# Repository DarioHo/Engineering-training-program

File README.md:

# Engineering-training-program

This is the Engineering training course that consists of three modules: Internet of Things, Microcontroller and Arduino, 
printed circuit board.

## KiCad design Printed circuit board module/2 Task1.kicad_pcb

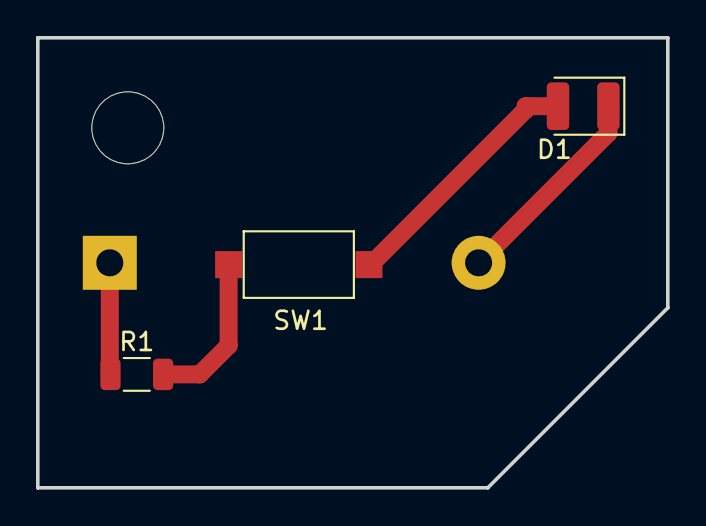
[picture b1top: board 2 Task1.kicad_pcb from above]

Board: 2 copper layers, 35.0 x 25.0 mm, 5 parts (1 on the bottom side), 4 nets.

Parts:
BT1: 103(CR2032); BatteryHolder_Keystone_103_1x20mm
D1: RED; LED_1210_3225Metric
H1: MountingHole; MountingHole_4mm
R1: 300R; R_1206_3216Metric
SW1: SW_Push; SW_SPST_CK_RS282G05A3

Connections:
unnamed: BT1.1, R1.1
unnamed: BT1.2, D1.1
unnamed: D1.2, SW1.1
unnamed: R1.2, SW1.2
